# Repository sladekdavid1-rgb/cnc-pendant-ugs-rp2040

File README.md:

# CNC Pendant for UGS / GRBL (RP2040, USB keyboard)

> 🇨🇿 **Česky:** kompletní návod krok za krokem je v [`NAVOD.html`](NAVOD.html) / [`NAVOD.pdf`](NAVOD.pdf).

A handheld jog pendant for small GRBL CNC machines (built for a **Lunyee/3018 Pro Ultra**) controlled from
**Universal Gcode Sender (UGS Platform)**. The pendant is a USB HID keyboard based on an RP2040 board: it presses
F13–F24 shortcuts (with Shift / Ctrl / Ctrl+Shift) that are bound to UGS actions. No drivers, no plugins,
no changes to GRBL.

Everything is designed to be made at home on a 3018-class machine: PCB isolation milling, an MDF registration jig,
an aluminium front panel engraved with a diode laser, and a 3D-printed enclosure.

|  |  |  |
|---|---|---|
| Laser-engraved aluminium panel | Board A (buttons) with LED board C | Board B (RP2040 + encoder) in the printed case |

## Features

- 21 buttons (3×7 diode matrix): axis select X/Y/Z, jog X±/Y±/Z±, F+/F−, START, HOLD, STOP, UNLOCK,
  HOME, return-to-zero, probe Z, zero X/Y/Z
- EC11 rotary encoder: jog the selected axis; **fast spinning temporarily increases the step**;
  with no axis selected it changes the jog feed; push = bigger/smaller step
- 19 LEDs via 3× 74HC595: selected axis, XY step (0.05 / 0.1 / 1 / 10 / 50 / 100 mm),
  Z step (0.05 / 0.1 / 1 / 10 mm), jog feed (10 / 100 / 1k / 2k / 3k / MAX mm/min)
- Step and feed are set in UGS **absolutely**, so the LEDs always match UGS
- Safety: START, HOME, RTZ, PROBE and ZERO require a **0.5 s hold**; jogging (arrows, encoder) is locked until an axis is selected – all other buttons always work;
  STOP and HOLD jump the key queue and discard pending jog steps
- Tap = one step, hold = continuous jog, **X + Y pressed together = diagonal jog**
- LEDs dim after 2 minutes idle (PWM on 595 OE); built-in **test mode** (hold STOP while plugging in)

## Hardware

| Board | Layers | Contents |
|---|---|---|
| **A – top** | double-sided | 21 switches 6×6 mm, 21× 1N4148W, 3× 74HC595 (SOIC-16) |
| **B – bottom** | single-sided | Laskakit Ultimate Pi Pico (RP2040), EC11E encoder, column pull-ups/filters |
| **C – LED** | single-sided, no jumpers | 19× LED 0603, 4 group resistors |

> **Note:** the LED group resistors R301–R304 (330 Ω / 820 Ω) are only a starting point. Tune them individually for the LEDs you use and the brightness you prefer (`LED_BRIGHT` in the firmware dims all groups equally).

Panel 95 × 65 mm, M3 mounting holes on an 88 × 58 mm grid. Full BOM: [`08_soupiska_BOM/BOM_CNC_pendant.csv`](08_soupiska_BOM/BOM_CNC_pendant.csv).

### RP2040 pin map

| Function | GPIO |
|---|---|
| Matrix rows ROW0–2 | GP2, GP3, GP4 |
| Matrix columns COL0–6 | GP5 … GP11 (internal pull-up + 10k on board B) |
| Encoder SW / B / A | GP13 / GP14 / GP15 |
| 74HC595 SER / SRCLK / RCLK / OE | GP18 / GP19 / GP20 / GP21 (OE = PWM brightness) |

## Boards

|  |  |  |
|---|---|---|
| A – top copper | B – copper (seen from top) | C – LED board |

All boards were cross-checked against the KiCad files (schematic ↔ PCB, Gerbers, isolation G-code simulation, drills, outlines) – see [`KONTROLA_DPS.md`](KONTROLA_DPS.md).

## Repository layout

| Folder | Contents |
|---|---|
| `00_obrazky` | photos of the finished build (`fotky/`), renders, PCB copper and placement images (generated from the KiCad files) |
| `01_DPS_KiCad` | KiCad 10 projects of boards A, B, C (+ custom footprints, iBOM) |
| `02_DPS_frezovani` | FlatCAM G-code in machining order (A1–A6, B1–B4, C1–C3), Gerbers, FlatCAM projects, Candle height maps |
| `03_pripravek_MDF` | MDF registration jig (DXF + Fusion G-code), 4 × Ø2.5 mm pins on 88 × 58 mm |
| `04_panel_cela` | aluminium panel: milling (Fusion G-code), laser (SVG all-in-one, LightBurn project, power/speed test), DXF |
| `05_krabicka_3D_tisk` | enclosure (STEP – slicers open it directly), OpenSCAD + Fusion script, hex standoffs, knob |
| `06_firmware_Arduino` | `cnc_pendant_v11` (recommended), `cnc_pendant` v10, test sketches |
| `07_UGS_zkratky` | 34 UGS keymap files (`.shadow`) |
| `08_soupiska_BOM` | BOM, LED resistor calculation |
| `nastroje` | Python tools: full PCB/G-code check (`kontrola.py`), board image renderer |

## Quick start

1. **Build the boards** – see `02_DPS_frezovani` and the guide. Boards are *not* plated: every via gets a wire and every
   THT pin that has a top trace must be soldered **on both sides**.
2. **Firmware** – Arduino IDE 2, board package *Raspberry Pi Pico/RP2040* by Earle Philhower
   (`https://github.com/earlephilhower/arduino-pico/releases/download/global/package_rp2040_index.json`),
   board *Raspberry Pi Pico*, USB Stack *Pico SDK*. Flash `06_firmware_Arduino/cnc_pendant_v11`.
   Test sketches first: `pendant_led_test`, `pendant_test` (types button names into Notepad).
3. **UGS shortcuts** – close UGS, copy all files from `07_UGS_zkratky/NetBeans/` to
   `%APPDATA%\ugsplatform\config\Keymaps\NetBeans\` (on Linux/macOS use the same `config/Keymaps/NetBeans` folder inside the UGS user directory),
   start UGS, check *Tools → Options → Keymap* (search `F13` → *Jog X+*). Enable *separate step size for Z*.
4. **Use it** – the UGS window must be focused (it is a keyboard). 2.5 s after plugging in, the pendant sets
   XY step 10 mm, Z step 1 mm, feed 1000 mm/min.

### Shortcut map

| Key | UGS action | Key | UGS action |
|---|---|---|---|
| F13/F14 | Jog X+/X− | Shift+F13/14/15 | Zero X/Y/Z |
| F15/F16 | Jog Y+/Y− | Shift+F16 | Probe Z |
| F17/F18 | Jog Z+/Z− | Shift+F17/F18 | Home / Return to zero |
| F21 | Pause/Resume | Shift+F19/F20/F21 | Jog feed ×10 / ÷10 / +1000 |
| F22/F23 | Start/Stop | Ctrl+F13…F16 | XY step 0.01/0.1/1/10 |
| F24 | Unlock | Ctrl+F17/F18 | XY step ×10 / + |
| Ctrl+Shift+F13…F16 | Diagonal X+Y+ / X+Y− / X−Y+ / X−Y− | Ctrl+F19…F22, F23 | Z step 0.01/0.1/1/10, Z + |

Other senders: anything that lets you bind keyboard shortcuts can use the pendant – only the keymap changes.

## Project status

**v1.0 – completed and archived (October 2026).** The project is kept ready for future changes:
see [`STAV_PROJEKTU.md`](STAV_PROJEKTU.md) (how to modify and re-check everything, open items, ideas) and [`CHANGELOG.md`](CHANGELOG.md).
After any PCB change run `python nastroje/kontrola.py` – it re-checks schematic ↔ PCB, DRC, Gerbers, isolation G-code and drills.

- The pendant is built and working (see photos): all 21 buttons and 19 LEDs tested, UGS keymap tested, laser-engraved panel done.
- Firmware **v11** passed host simulation but is **not yet tested on hardware** – v10 is the fallback.
- Case, hex standoffs and knob are printed and fitted (see photos).

Issues, photos of your builds and improvements are welcome.

## How it was made

Designed and built by me with the help of an AI assistant (Claude) for the schematics, firmware and documentation. Everything was manufactured and tested on real hardware.

## License

- Hardware, mechanical parts, G-code and documentation: **CC BY-SA 4.0** – see [`LICENSE`](LICENSE)
- Firmware (`06_firmware_Arduino`): **MIT** – see [`06_firmware_Arduino/LICENSE`](06_firmware_Arduino/LICENSE)

© 2026 David Sládek

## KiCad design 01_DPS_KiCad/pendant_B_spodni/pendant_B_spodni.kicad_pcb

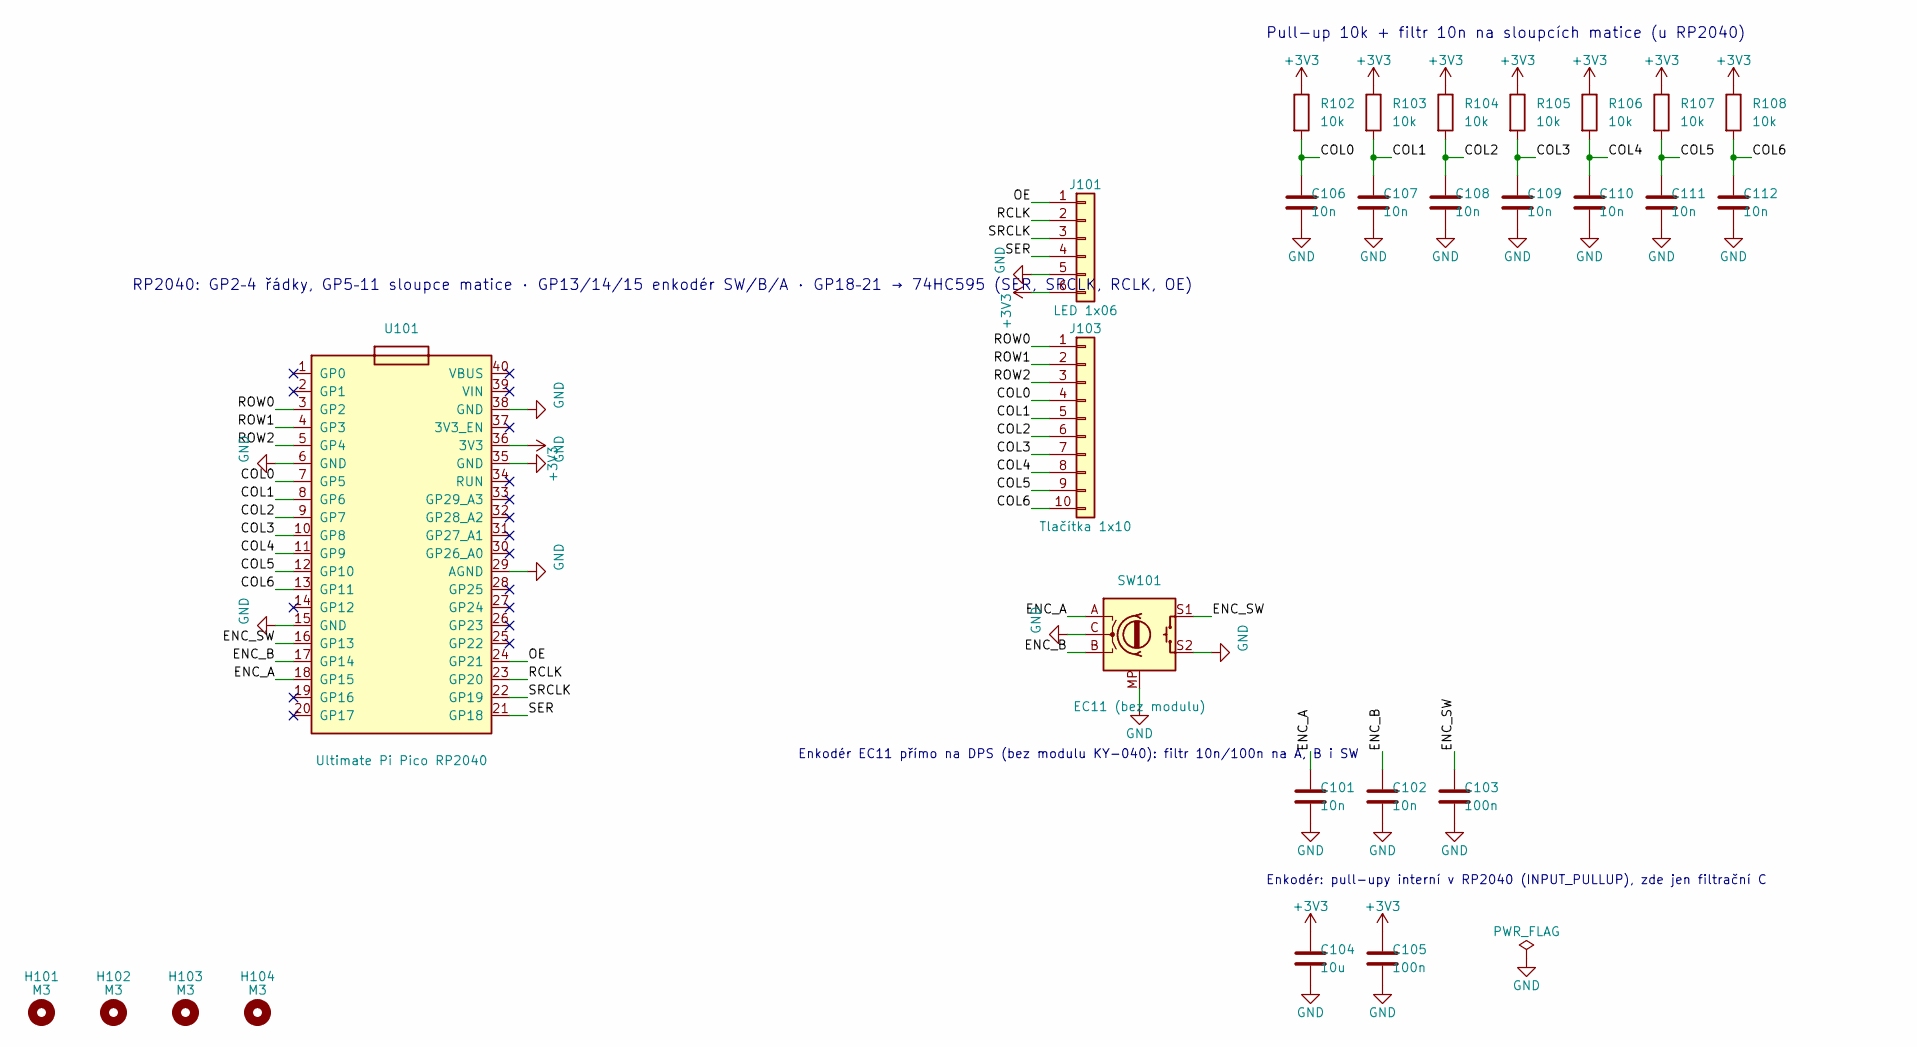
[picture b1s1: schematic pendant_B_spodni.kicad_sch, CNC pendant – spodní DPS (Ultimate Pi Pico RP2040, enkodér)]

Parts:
C101, C102, C106, C107, C108, C109, C110, C111, C112: 10n; C_0805_2012Metric
C103, C105: 100n; C_0805_2012Metric
C104: 10u; C_0805_2012Metric
H101, H102, H103, H104: M3; MountingHole_3.2mm_M3
J101: LED 1x06; PinHeader_1x06_P2.54mm_Vertical
J103: Tlačítka 1x10; PinHeader_1x10_P2.54mm_Vertical
R102, R103, R104, R105, R106, R107, R108: 10k; R_0805_2012Metric
SW101: EC11 (bez modulu); RotaryEncoder_Alps_EC11E-Switch_Vertical_H20mm
U101: Ultimate Pi Pico RP2040; Ultimate_Pico_2x20_W17.78

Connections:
+3V3: C104.1, C105.1, J101.6, R102.1, R103.1, R104.1, R105.1, R106.1, R107.1, R108.1, U101.36 (3V3)
/COL0: C106.1, J103.4, R102.2, U101.7 (GP5)
/COL1: C107.1, J103.5, R103.2, U101.8 (GP6)
/COL2: C108.1, J103.6, R104.2, U101.9 (GP7)
/COL3: C109.1, J103.7, R105.2, U101.10 (GP8)
/COL4: C110.1, J103.8, R106.2, U101.11 (GP9)
/COL5: C111.1, J103.9, R107.2, U101.12 (GP10)
/COL6: C112.1, J103.10, R108.2, U101.13 (GP11)
/ENC_A: C101.1, SW101.A, U101.18 (GP15)
/ENC_B: C102.1, SW101.B, U101.17 (GP14)
/ENC_SW: C103.1, SW101.S1, U101.16 (GP13)
/OE: J101.1, U101.24 (GP21)
/RCLK: J101.2, U101.23 (GP20)
/ROW0: J103.1, U101.3 (GP2)
/ROW1: J103.2, U101.4 (GP3)
/ROW2: J103.3, U101.5 (GP4)
/SER: J101.4, U101.21 (GP18)
/SRCLK: J101.3, U101.22 (GP19)
GND: C101.2, C102.2, C103.2, C104.2, C105.2, C106.2, C107.2, C108.2, C109.2, C110.2, C111.2, C112.2, J101.5, SW101.C, SW101.MP, SW101.S2, U101.6 (GND), U101.15 (GND), U101.29 (AGND), U101.35 (GND), U101.38 (GND)

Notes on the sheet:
RP2040: GP2–4 řádky, GP5–11 sloupce matice · GP13/14/15 enkodér SW/B/A · GP18–21 → 74HC595 (SER, SRCLK, RCLK, OE)
Pull-up 10k + filtr 10n na sloupcích matice (u RP2040)
Enkodér EC11 přímo na DPS (bez modulu KY-040): filtr 10n/100n na A, B i SW
Enkodér: pull-upy interní v RP2040 (INPUT_PULLUP), zde jen filtrační C

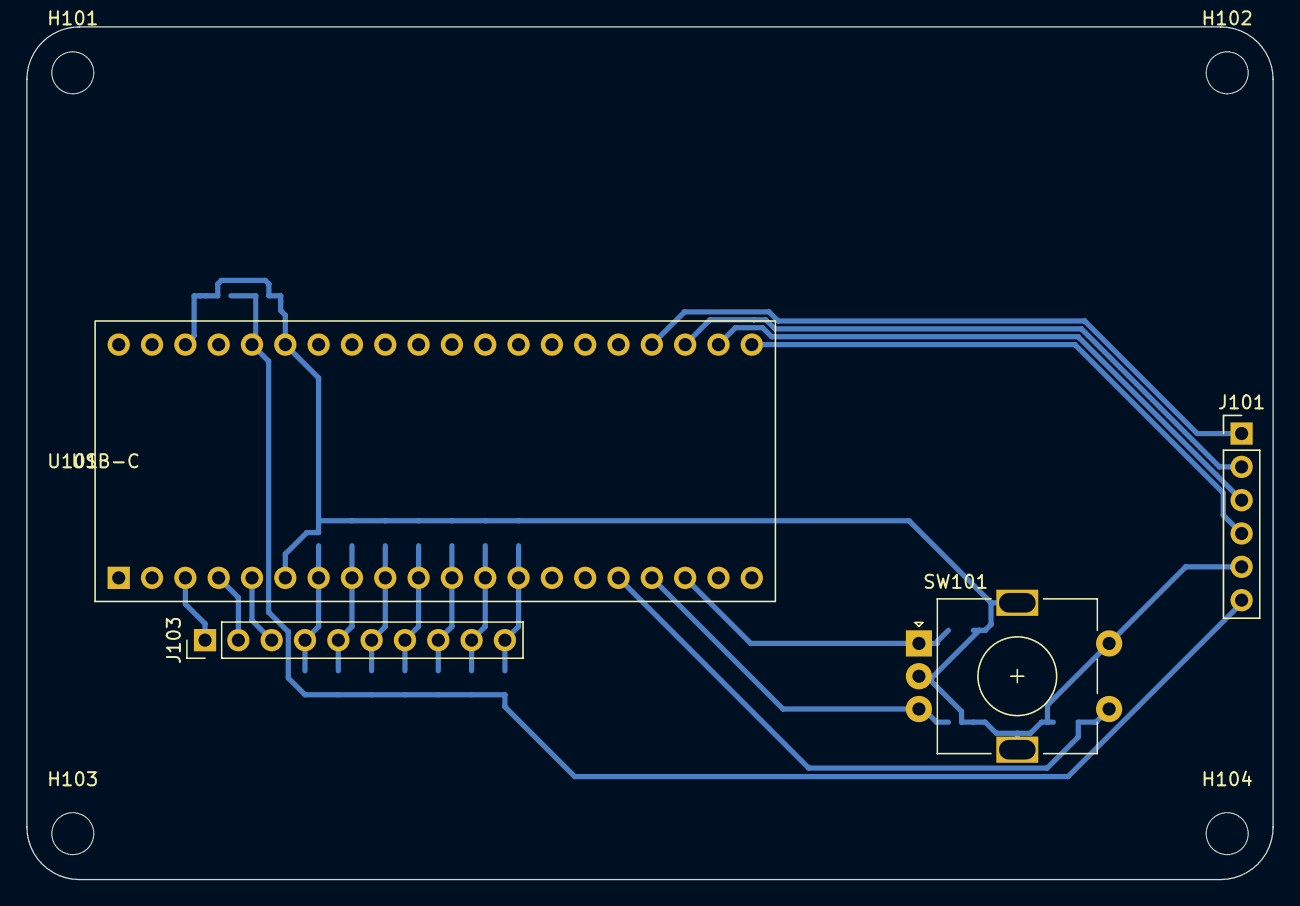
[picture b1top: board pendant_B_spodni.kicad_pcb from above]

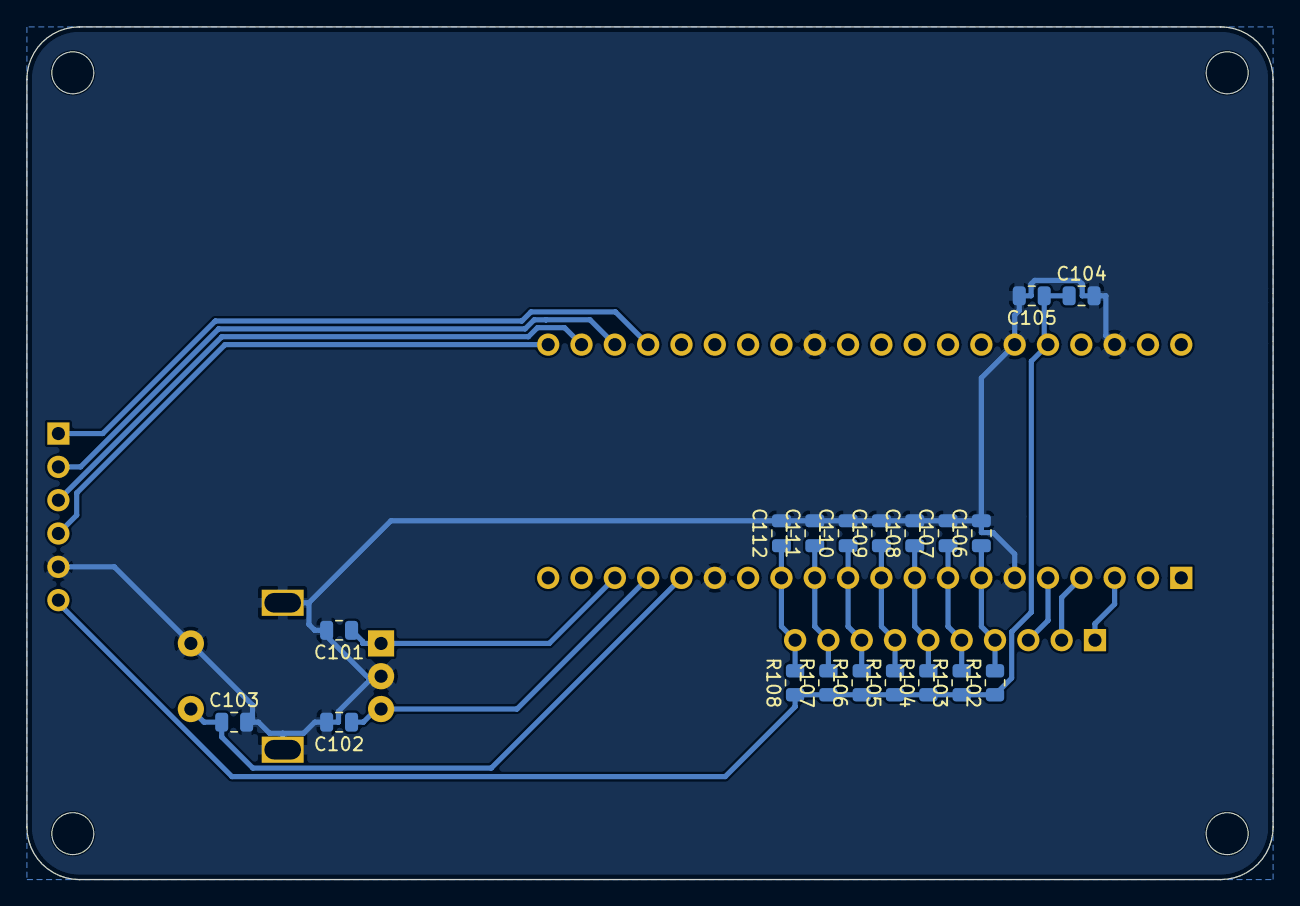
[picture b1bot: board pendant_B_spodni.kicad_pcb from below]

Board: 2 copper layers, 95.0 x 65.0 mm, 27 parts (19 on the bottom side), 19 nets.

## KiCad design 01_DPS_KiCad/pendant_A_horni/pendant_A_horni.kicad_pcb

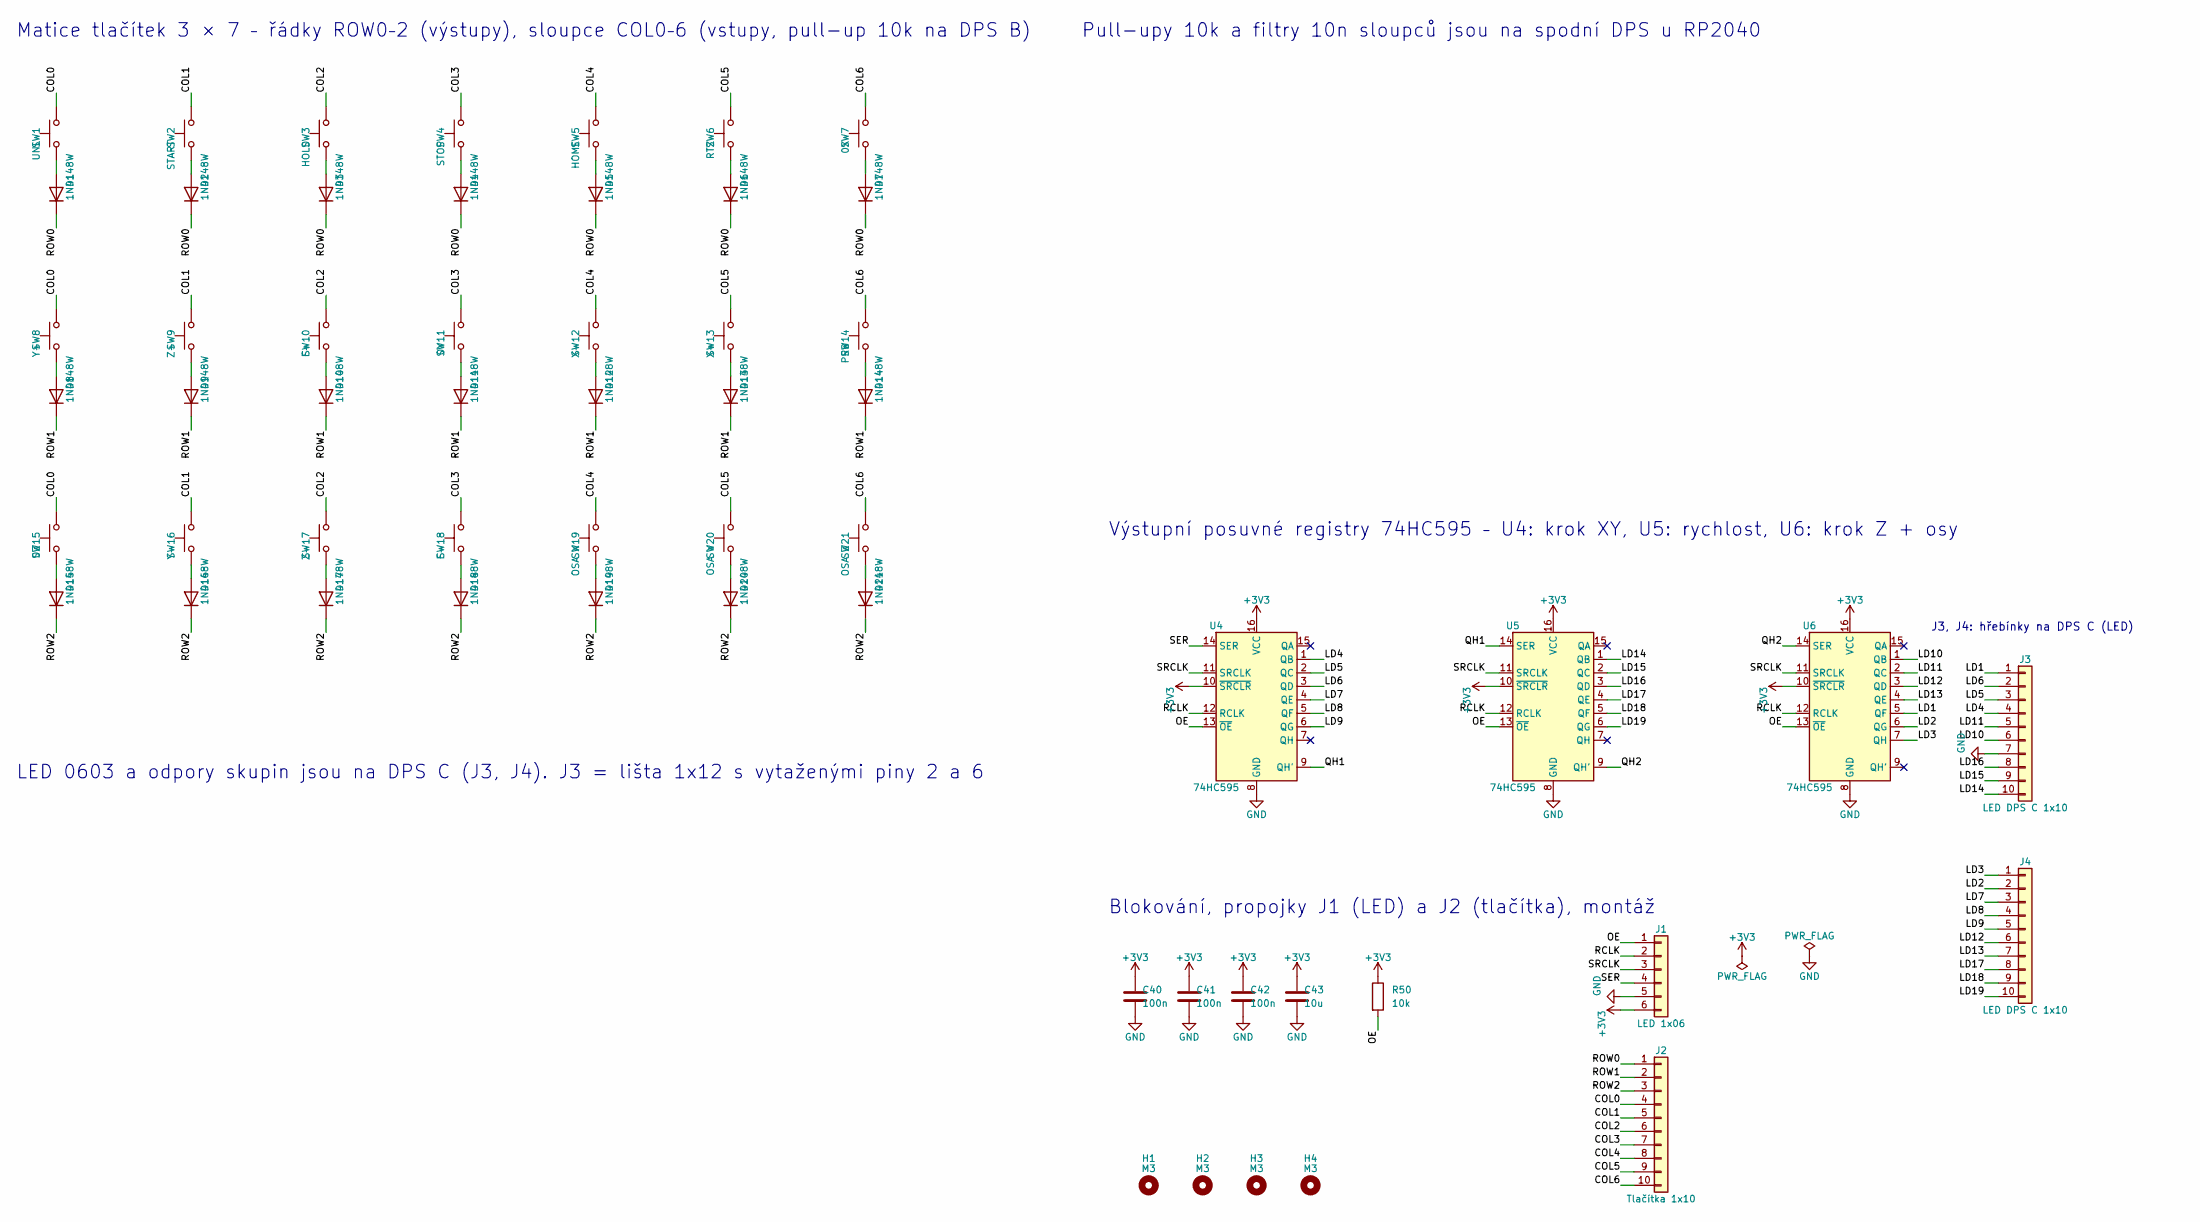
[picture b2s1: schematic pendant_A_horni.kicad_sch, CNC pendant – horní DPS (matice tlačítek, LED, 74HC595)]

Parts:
C40, C41, C42: 100n; C_0805_2012Metric
C43: 10u; C_0805_2012Metric
D1, D2, D3, D4, D5, D6, D7, D8, D9, D10, D11, D12, D13, D14, D15, D16, D17, D18, D19, D20, D21: 1N4148W; D_SOD-123
H1, H2, H3, H4: M3; MountingHole_3.2mm_M3
J1: LED 1x06; PinHeader_1x06_P2.54mm_Vertical
J2: Tlačítka 1x10; PinHeader_1x10_P2.54mm_Vertical
J3: LED DPS C 1x10; PinHeader_1x12_P2.54mm_10pinu
J4: LED DPS C 1x10; PinHeader_1x10_P2.54mm_Vertical
R50: 10k; R_0805_2012Metric
SW1: UNL; SW_PUSH_6mm
SW2: START; SW_PUSH_6mm
SW3: HOLD; SW_PUSH_6mm
SW4: STOP; SW_PUSH_6mm
SW5: HOME; SW_PUSH_6mm
SW6: RTZ; SW_PUSH_6mm
SW7: 0X; SW_PUSH_6mm
SW8: Y+; SW_PUSH_6mm
SW9: Z+; SW_PUSH_6mm
SW10: F+; SW_PUSH_6mm
SW11: 0Y; SW_PUSH_6mm
SW12: X-; SW_PUSH_6mm
SW13: X+; SW_PUSH_6mm
SW14: PRB; SW_PUSH_6mm
SW15: 0Z; SW_PUSH_6mm
SW16: Y-; SW_PUSH_6mm
SW17: Z-; SW_PUSH_6mm
SW18: F-; SW_PUSH_6mm
SW19: OSA X; SW_PUSH_6mm
SW20: OSA Y; SW_PUSH_6mm
SW21: OSA Z; SW_PUSH_6mm
U4, U5, U6: 74HC595; SOIC-16_3.9x9.9mm_P1.27mm

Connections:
+3V3: C40.1, C41.1, C42.1, C43.1, J1.6, R50.1, U4.10 (~SRCLR), U4.16 (VCC), U5.10 (~SRCLR), U5.16 (VCC), U6.10 (~SRCLR), U6.16 (VCC)
/COL0: J2.4, SW1.2, SW8.2, SW15.2
/COL1: J2.5, SW2.2, SW9.2, SW16.2
/COL2: J2.6, SW3.2, SW10.2, SW17.2
/COL3: J2.7, SW4.2, SW11.2, SW18.2
/COL4: J2.8, SW5.2, SW12.2, SW19.2
/COL5: J2.9, SW6.2, SW13.2, SW20.2
/COL6: J2.10, SW7.2, SW14.2, SW21.2
/LD1: J3.1, U6.5 (QF)
/LD2: J4.2, U6.6 (QG)
/LD3: J4.1, U6.7 (QH)
/LD4: J3.4, U4.1 (QB)
/LD5: J3.3, U4.2 (QC)
/LD6: J3.2, U4.3 (QD)
/LD7: J4.3, U4.4 (QE)
/LD8: J4.4, U4.5 (QF)
/LD9: J4.5, U4.6 (QG)
/LD10: J3.6, U6.1 (QB)
/LD11: J3.5, U6.2 (QC)
/LD12: J4.6, U6.3 (QD)
/LD13: J4.7, U6.4 (QE)
/LD14: J3.10, U5.1 (QB)
/LD15: J3.9, U5.2 (QC)
/LD16: J3.8, U5.3 (QD)
/LD17: J4.8, U5.4 (QE)
/LD18: J4.9, U5.5 (QF)
/LD19: J4.10, U5.6 (QG)
/OE: J1.1, R50.2, U4.13 (~OE), U5.13 (~OE), U6.13 (~OE)
/QH1: U4.9 (QH'), U5.14 (SER)
/QH2: U5.9 (QH'), U6.14 (SER)
/RCLK: J1.2, U4.12 (RCLK), U5.12 (RCLK), U6.12 (RCLK)
/ROW0: D1.1 (K), D2.1 (K), D3.1 (K), D4.1 (K), D5.1 (K), D6.1 (K), D7.1 (K), J2.1
/ROW1: D8.1 (K), D9.1 (K), D10.1 (K), D11.1 (K), D12.1 (K), D13.1 (K), D14.1 (K), J2.2
/ROW2: D15.1 (K), D16.1 (K), D17.1 (K), D18.1 (K), D19.1 (K), D20.1 (K), D21.1 (K), J2.3
/SER: J1.4, U4.14 (SER)
/SRCLK: J1.3, U4.11 (SRCLK), U5.11 (SRCLK), U6.11 (SRCLK)
GND: C40.2, C41.2, C42.2, C43.2, J1.5, J3.7, U4.8 (GND), U5.8 (GND), U6.8 (GND)
unnamed: D1.2 (A), SW1.1
unnamed: D2.2 (A), SW2.1
unnamed: D3.2 (A), SW3.1
unnamed: D4.2 (A), SW4.1
unnamed: D5.2 (A), SW5.1
unnamed: D6.2 (A), SW6.1
unnamed: D7.2 (A), SW7.1
unnamed: D8.2 (A), SW8.1
unnamed: D9.2 (A), SW9.1
unnamed: D10.2 (A), SW10.1
unnamed: D11.2 (A), SW11.1
unnamed: D12.2 (A), SW12.1
unnamed: D13.2 (A), SW13.1
unnamed: D14.2 (A), SW14.1
unnamed: D15.2 (A), SW15.1
unnamed: D16.2 (A), SW16.1
unnamed: D17.2 (A), SW17.1
unnamed: D18.2 (A), SW18.1
unnamed: D19.2 (A), SW19.1
unnamed: D20.2 (A), SW20.1
unnamed: D21.2 (A), SW21.1

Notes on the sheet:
Matice tlačítek 3 × 7 – řádky ROW0–2 (výstupy), sloupce COL0–6 (vstupy, pull-up 10k na DPS B)
Pull-upy 10k a filtry 10n sloupců jsou na spodní DPS u RP2040
Výstupní posuvné registry 74HC595 – U4: krok XY, U5: rychlost, U6: krok Z + osy
LED 0603 a odpory skupin jsou na DPS C (J3, J4). J3 = lišta 1x12 s vytaženými piny 2 a 6
Blokování, propojky J1 (LED) a J2 (tlačítka), montáž
J3, J4: hřebínky na DPS C (LED)

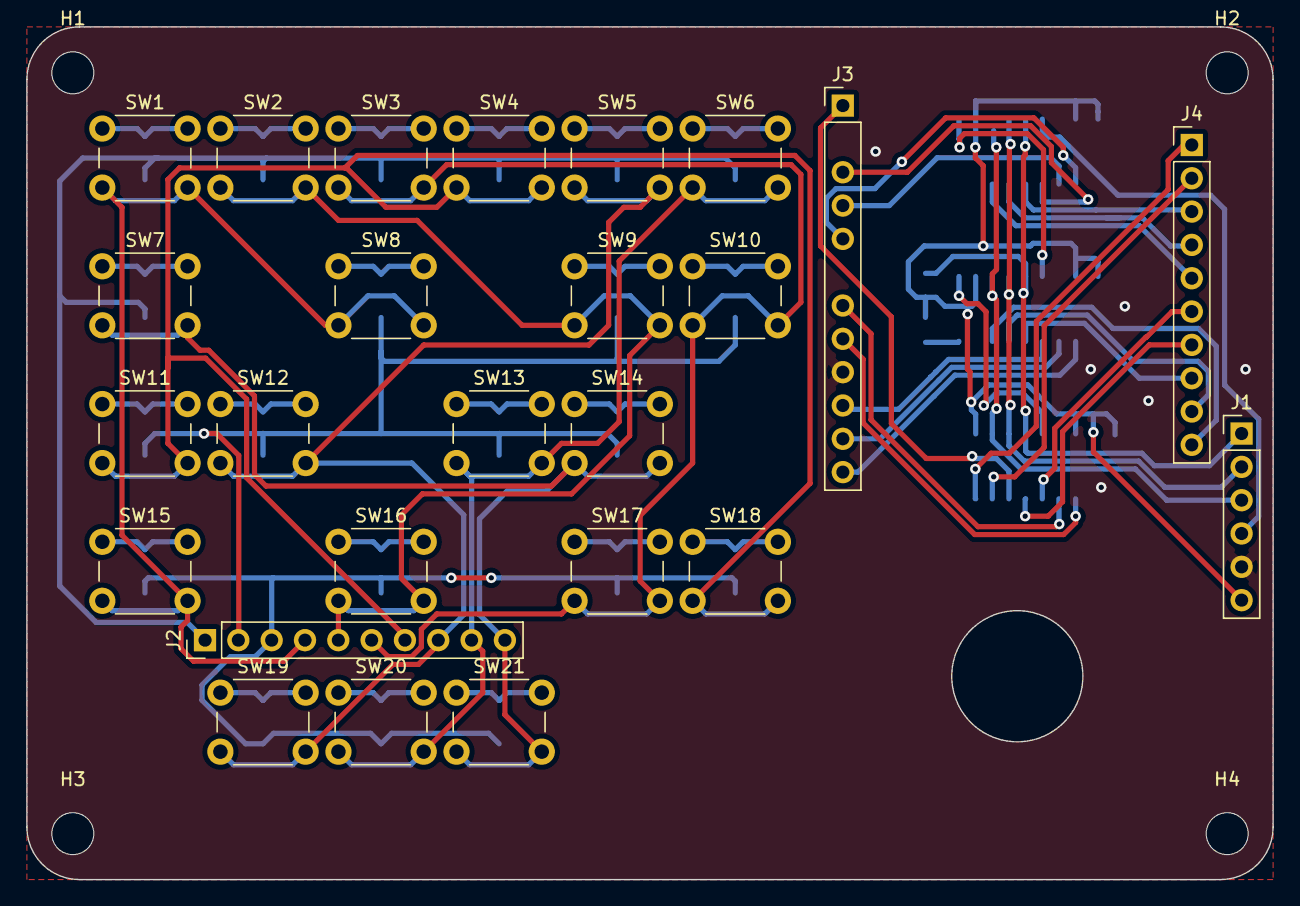
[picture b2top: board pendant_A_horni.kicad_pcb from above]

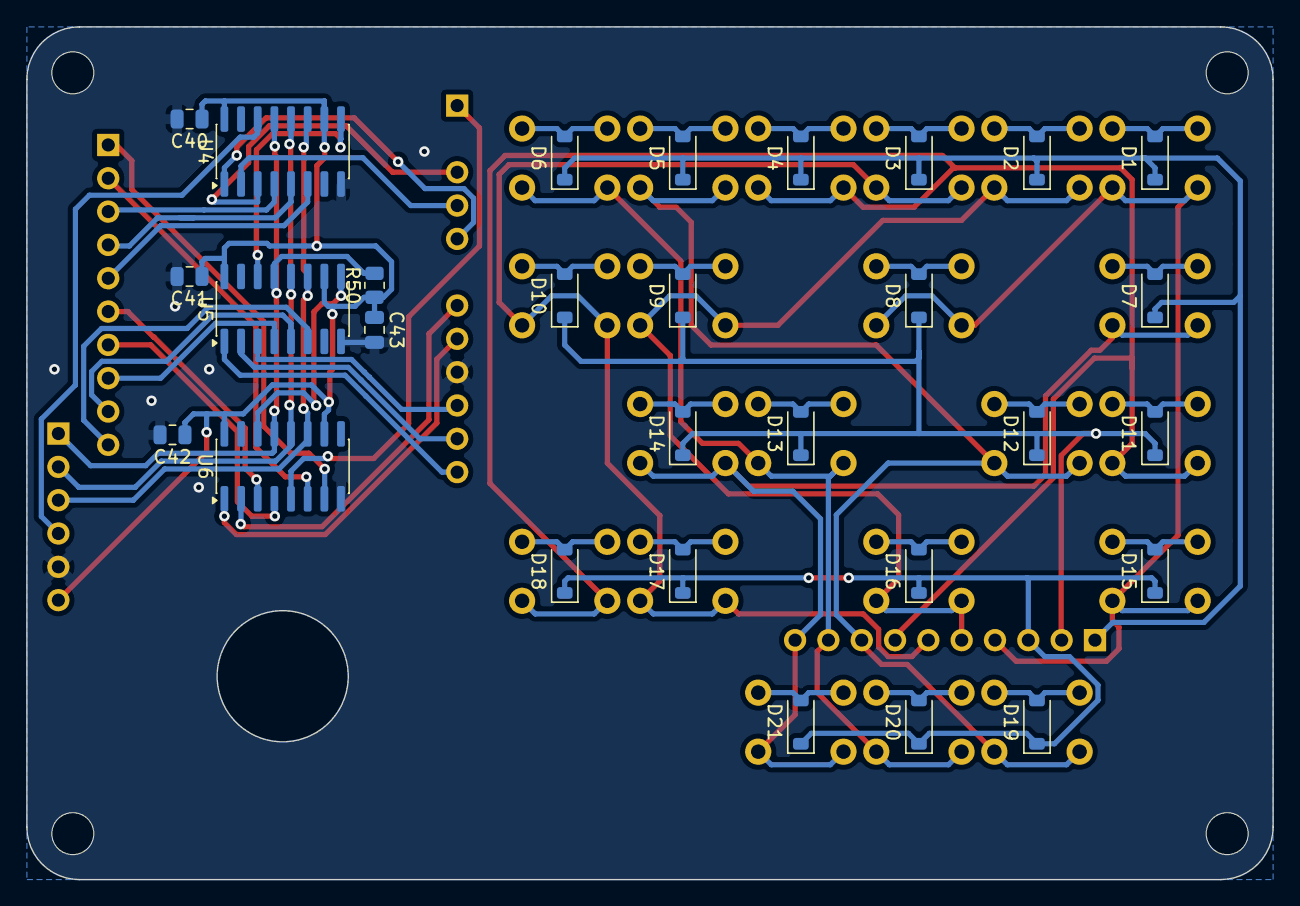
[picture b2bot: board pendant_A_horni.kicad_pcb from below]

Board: 2 copper layers, 95.0 x 65.0 mm, 58 parts (29 on the bottom side), 58 nets.

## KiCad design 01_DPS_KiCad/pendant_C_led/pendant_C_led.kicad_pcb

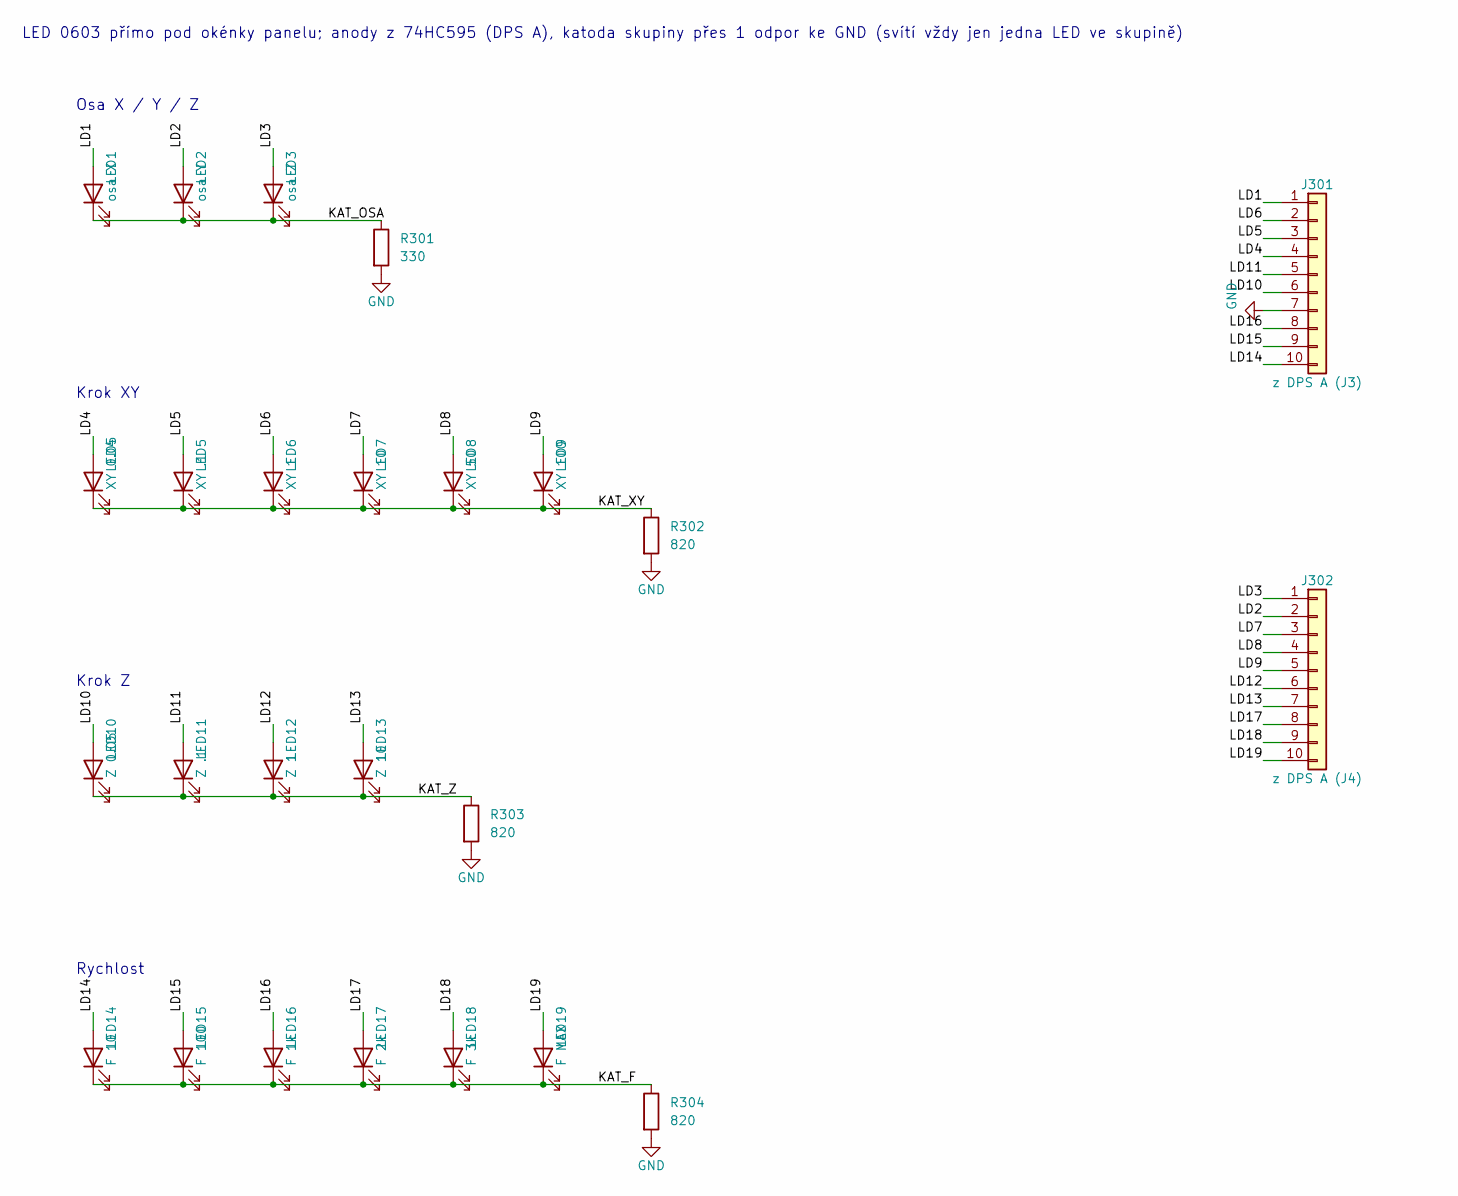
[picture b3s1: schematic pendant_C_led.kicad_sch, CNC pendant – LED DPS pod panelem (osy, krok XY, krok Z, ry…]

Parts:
J301: z DPS A (J3); PinHeader_1x12_P2.54mm_10pinu
J302: z DPS A (J4); PinHeader_1x10_P2.54mm_Vertical
LED1: osa X; LED_0603_1608Metric
LED2: osa Y; LED_0603_1608Metric
LED3: osa Z; LED_0603_1608Metric
LED4: XY 0.05; LED_0603_1608Metric
LED5: XY .1; LED_0603_1608Metric
LED6: XY 1; LED_0603_1608Metric
LED7: XY 10; LED_0603_1608Metric
LED8: XY 50; LED_0603_1608Metric
LED9: XY 100; LED_0603_1608Metric
LED10: Z 0.05; LED_0603_1608Metric
LED11: Z .1; LED_0603_1608Metric
LED12: Z 1; LED_0603_1608Metric
LED13: Z 10; LED_0603_1608Metric
LED14: F 10; LED_0603_1608Metric
LED15: F 100; LED_0603_1608Metric
LED16: F 1k; LED_0603_1608Metric
LED17: F 2k; LED_0603_1608Metric
LED18: F 3k; LED_0603_1608Metric
LED19: F MAX; LED_0603_1608Metric
R301: 330; R_0603_1608Metric
R302, R303, R304: 820; R_0603_1608Metric

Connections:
/KAT_F: LED14.1 (K), LED15.1 (K), LED16.1 (K), LED17.1 (K), LED18.1 (K), LED19.1 (K), R304.1
/KAT_OSA: LED1.1 (K), LED2.1 (K), LED3.1 (K), R301.1
/KAT_XY: LED4.1 (K), LED5.1 (K), LED6.1 (K), LED7.1 (K), LED8.1 (K), LED9.1 (K), R302.1
/KAT_Z: LED10.1 (K), LED11.1 (K), LED12.1 (K), LED13.1 (K), R303.1
/LD1: J301.1, LED1.2 (A)
/LD2: J302.2, LED2.2 (A)
/LD3: J302.1, LED3.2 (A)
/LD4: J301.4, LED4.2 (A)
/LD5: J301.3, LED5.2 (A)
/LD6: J301.2, LED6.2 (A)
/LD7: J302.3, LED7.2 (A)
/LD8: J302.4, LED8.2 (A)
/LD9: J302.5, LED9.2 (A)
/LD10: J301.6, LED10.2 (A)
/LD11: J301.5, LED11.2 (A)
/LD12: J302.6, LED12.2 (A)
/LD13: J302.7, LED13.2 (A)
/LD14: J301.10, LED14.2 (A)
/LD15: J301.9, LED15.2 (A)
/LD16: J301.8, LED16.2 (A)
/LD17: J302.8, LED17.2 (A)
/LD18: J302.9, LED18.2 (A)
/LD19: J302.10, LED19.2 (A)
GND: J301.7, R301.2, R302.2, R303.2, R304.2

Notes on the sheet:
LED 0603 přímo pod okénky panelu; anody z 74HC595 (DPS A), katoda skupiny přes 1 odpor ke GND (svítí vždy jen jedna LED ve skupině)
Osa X / Y / Z
Krok XY
Krok Z
Rychlost

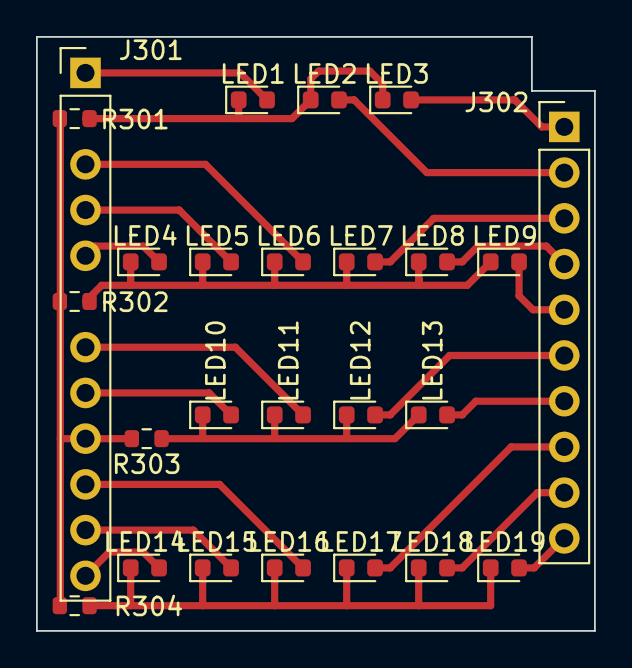
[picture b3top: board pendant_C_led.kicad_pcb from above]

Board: 2 copper layers, 31.0 x 33.0 mm, 25 parts (0 on the bottom side), 24 nets.

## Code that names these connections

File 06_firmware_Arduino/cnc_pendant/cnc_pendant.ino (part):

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
// ---------------- Piny ----------------
// piny zvolené pro jednovrstvou DPS B (v13)
const uint8_t PIN_ENC_A  = 15;   // CLK  (pin 18 klonu)
const uint8_t PIN_ENC_B  = 14;   // DT   (pin 17)
const uint8_t PIN_ENC_SW = 13;   // SW   (pin 16) (krátce = větší krok, dlouze = menší)

const uint8_t PIN_595_DATA  = 18; // SER   (pin 14 prvního 595)
const uint8_t PIN_595_CLK   = 19; // SRCLK (pin 11 všech)
const uint8_t PIN_595_LATCH = 20; // RCLK  (pin 12 všech)
const uint8_t PIN_595_OE    = 21; // OE    (pin 13 všech, R50 10k na 3V3; LOW = svítí)
const uint8_t LED_BRIGHT    = 255; // jas LED 0..255 (PWM na OE)

const uint8_t ROW_PINS[3] = { 2, 3, 4 };                    // řádky ROW0-2 (aktivní LOW)
const uint8_t COL_PINS[7] = { 5, 6, 7, 8, 9, 10, 11 };      // sloupce COL0-6 (ext. pull-up 10k + 10n)
const uint16_t ROW_SETTLE_US = 500;  // RC sloupce 10k×10n = 0,1 ms → počkat 5τ

// ---------------- Klávesy v UGS ----------------
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const int8_t QDEC[16] = { 0,-1, 1, 0,  1, 0, 0,-1,  -1, 0, 0, 1,  0, 1,-1, 0 };

void encIsr() {
  uint8_t s = (digitalRead(PIN_ENC_A) << 1) | digitalRead(PIN_ENC_B);
  encEdges += QDEC[(encState << 2) | s];
  encState = s;
}
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
// ---------------- Setup ----------------
void setup() {
  pinMode(PIN_ENC_A, INPUT_PULLUP);
  pinMode(PIN_ENC_B, INPUT_PULLUP);
  pinMode(PIN_ENC_SW, INPUT_PULLUP);
  pinMode(PIN_595_DATA, OUTPUT);
  pinMode(PIN_595_CLK, OUTPUT);
  pinMode(PIN_595_LATCH, OUTPUT);
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  writeLeds(0);
  pinMode(PIN_595_OE, OUTPUT);
  analogWrite(PIN_595_OE, 255 - LED_BRIGHT);   // OE je aktivní v LOW
  encState = (digitalRead(PIN_ENC_A) << 1) | digitalRead(PIN_ENC_B);
  attachInterrupt(digitalPinToInterrupt(PIN_ENC_A), encIsr, CHANGE);
  attachInterrupt(digitalPinToInterrupt(PIN_ENC_B), encIsr, CHANGE);
  Keyboard.begin();
}

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
  // tlačítko enkodéru: krátce větší krok, dlouze menší
  // zvolená osa Z mění krok Z, jinak krok XY
  bool r = digitalRead(PIN_ENC_SW);
  if (r != encSwRaw) { encSwRaw = r; encSwChanged = now; }
  if (r != encSwStable && now - encSwChanged >= DEBOUNCE_MS) {
    encSwStable = r;
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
